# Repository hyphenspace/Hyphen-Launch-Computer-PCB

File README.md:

## Hyphen Launch Computer PCB

Eagle CAD files for the Hyphen Launch Computer.

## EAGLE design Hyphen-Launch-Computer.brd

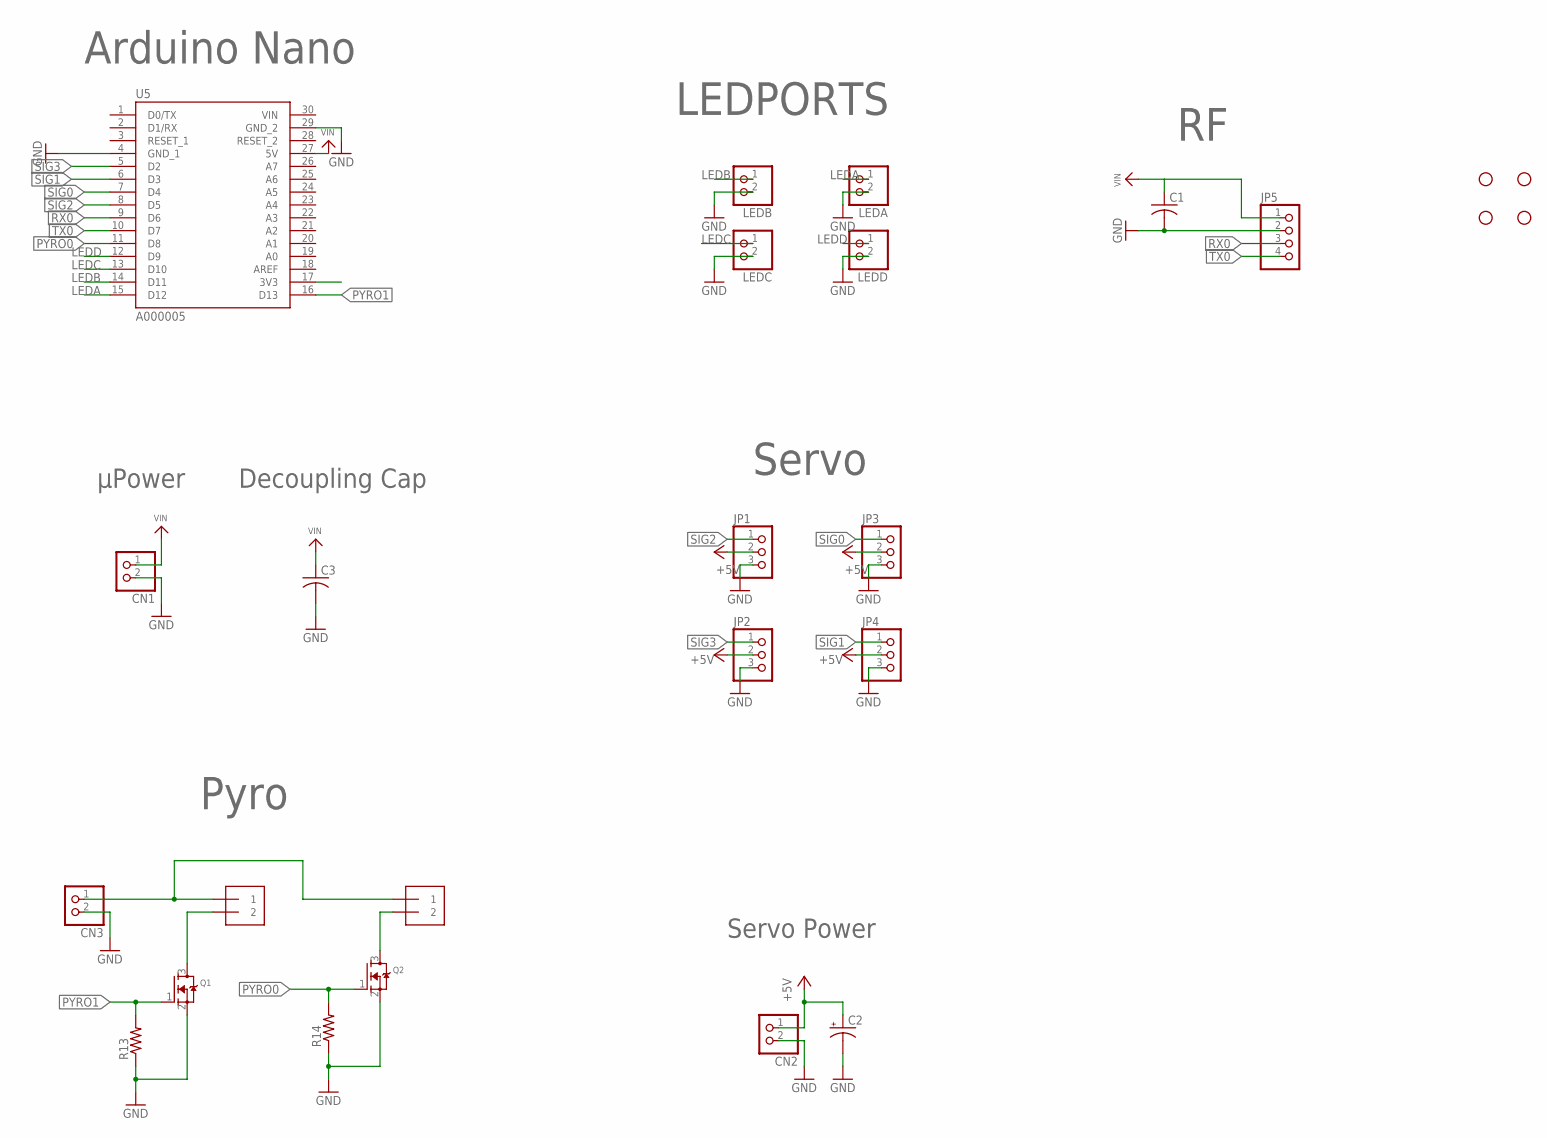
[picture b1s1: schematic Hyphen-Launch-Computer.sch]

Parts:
C1, C3: C-USC0805; C0805
C2: CPOL-USE3.5-8; E3,5-8
CN1, CN2, CN3: JST_2PIN-SMT-RA; JST-PH-2-SMT-RA
H1, H2, H3, H4: STAND-OFF
J2, J6: 1X2-3.5MM
JP1, JP2, JP3, JP4: PINHD-1X3; 1X03
JP5: PINHD-1X4; 1X04
LEDA: JST_2PIN-SMT-RA; JST-PH-2-SMT-RA
LEDB: JST_2PIN-SMT-RA; JST-PH-2-SMT-RA
LEDC: JST_2PIN-SMT-RA; JST-PH-2-SMT-RA
LEDD: JST_2PIN-SMT-RA; JST-PH-2-SMT-RA
Q1, Q2: MOSFET-NREFLOW; SOT23
R13, R14: R-US_M0805; M0805
U5: A000005; MODULE_A000005

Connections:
+5V: C2.+, CN2.1 (2), JP1.2, JP2.2, JP3.2, JP4.2
GND: C1.2, C2.-, C3.2, CN1.2 (1), CN2.2 (1), CN3.2 (1), JP1.3, JP2.3, JP3.3, JP4.3, JP5.2, LEDA.2 (1), LEDB.2 (1), LEDC.2 (1), LEDD.2 (1), Q1.2 (S), Q2.2 (S), R13.1, R14.1, U5.4 (GND_1), U5.29 (GND_2)
LEDA: LEDA.1 (2), U5.15 (D12)
LEDB: LEDB.1 (2), U5.14 (D11)
LEDC: LEDC.1 (2), U5.13 (D10)
LEDD: LEDD.1 (2), U5.12 (D9)
unnamed: CN3.1 (2), J2.1, J6.1
unnamed: J2.2, Q1.3 (D)
unnamed: J6.2, Q2.3 (D)
PYRO0: Q2.1 (G), R14.2, U5.11 (D8)
PYRO1: Q1.1 (G), R13.2, U5.16 (D13)
RX0: JP5.3, U5.9 (D6)
SIG0: JP3.1, U5.7 (D4)
SIG1: JP4.1, U5.6 (D3)
SIG2: JP1.1, U5.8 (D5)
SIG3: JP2.1, U5.5 (D2)
TX0: JP5.4, U5.10 (D7)
VIN: C1.1, C3.1, CN1.1 (2), JP5.1, U5.27 (5V), U5.30 (VIN)

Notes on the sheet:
μPower
LEDPORTS
Decoupling Cap
Pyro
Servo
Servo Power
Arduino Nano

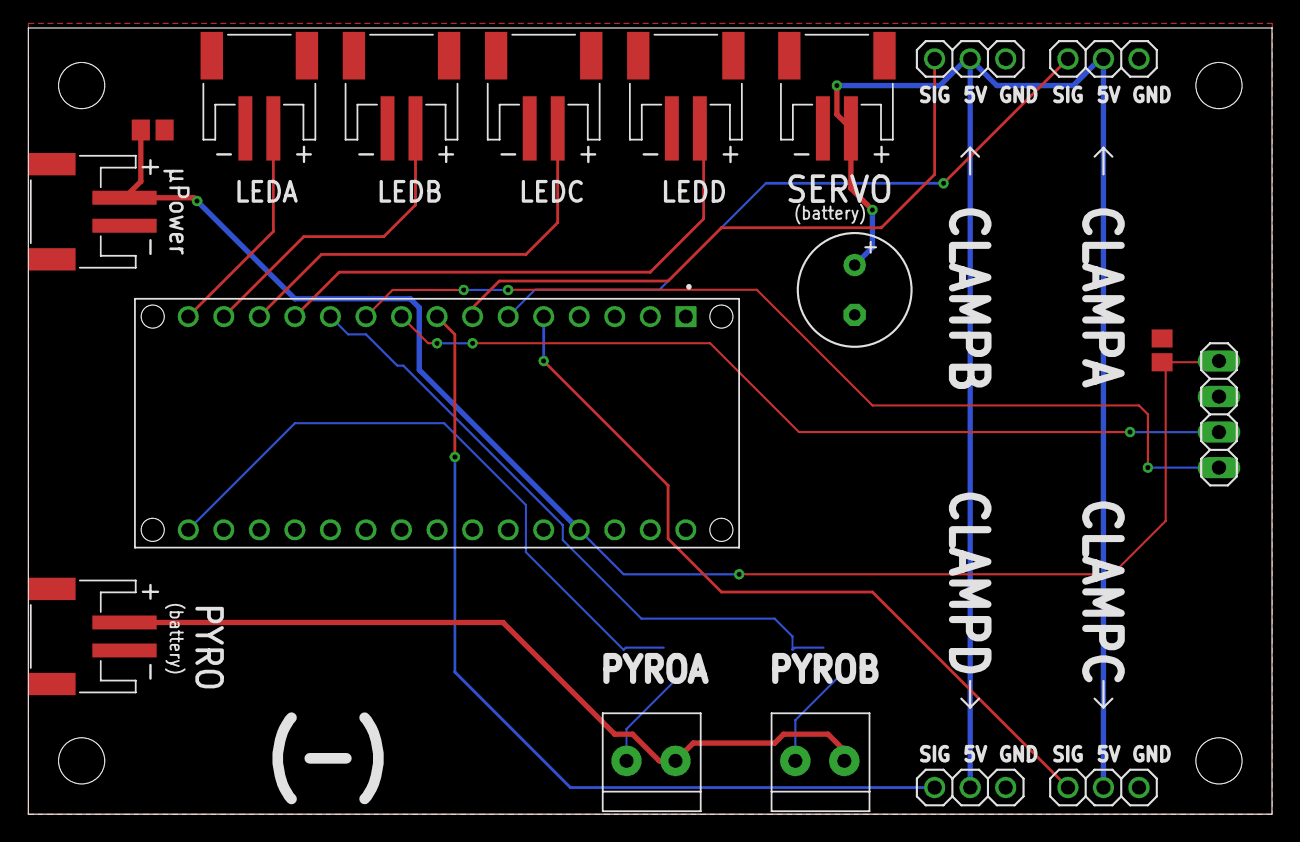
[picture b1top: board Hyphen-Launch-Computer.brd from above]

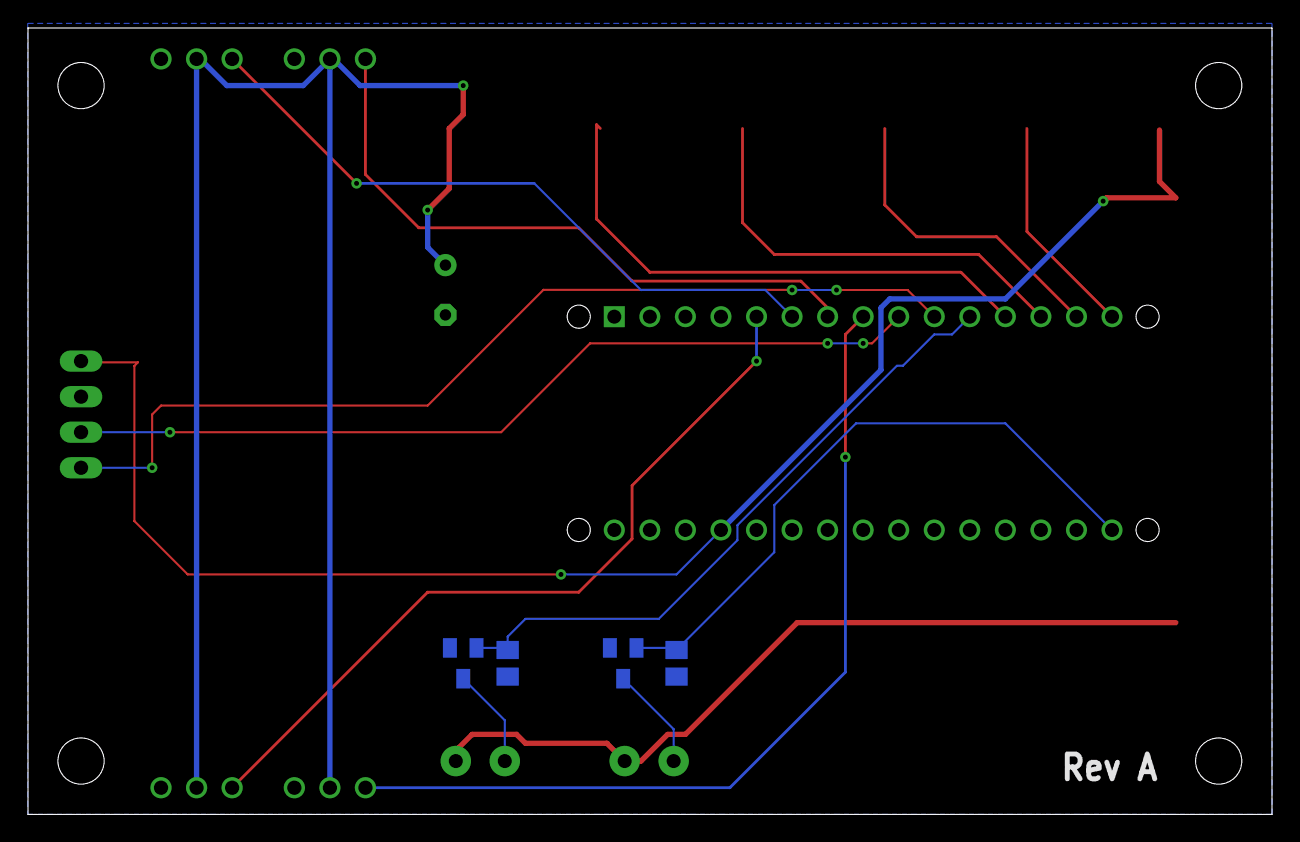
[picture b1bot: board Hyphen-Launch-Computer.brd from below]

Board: 2 copper layers, 88.9 x 56.2 mm, 26 parts (4 on the bottom side), 18 nets.

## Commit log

2020-11-06 Added CAD files and a photo ✨
2020-11-07 Created parts list file
2020-11-07 Update and rename Hyphen-Launch-Computer-PCB.txt to Hyphen-Launch-Computer-Parts-List.txt
    Updated the file name for clarity

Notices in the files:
parts and their libraries:
SparkFun-Hardware: Licensing: Creative Commons ShareAlike 4.0 International - https://creativecommons.org/licenses/by-sa/4.0
microbuilder: This work is placed in the public domain, and may be freely used for commercial and non-commercial work with the following conditions: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
